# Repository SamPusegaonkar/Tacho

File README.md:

# TachoMeter

**The above code is written in Arduino C Language.**

**Description**: A tachometer is a device used to measure the rpm of a motor or any other rotating machine. The lack of a tachometer on my bike was the inspiration for this project.   <br/>

  **Apparatus**:     
  
    1. A microcontroller
    2. Multi-colored RGB LED
    3. IR sensor
    4. Some white tape
    5. Cardboard
                     
  **Instructions**: 
  
    1. Cut a circle on a piece of cardboard and attach some white tape from the radius of the circle to its end.
    2. Attach this circle on the shaft of the motor.
    3. Place in infrared sensor near the circle such that the tape passes atleast once, when the motor shaft rotates.
    4. I suck at explaning, so watch the video provided in the repo.

  **Multi-Colored RGB LED as output**:
  
    * if 0-10   rpm: then white 
    * if 10-20  rpm: then pink 
    * if 20-30  rpm: then red
    * if 30-40  rpm: then orange
    * if 40-50  rpm: then yellow
    * if 50-60  rpm: then blue
    * if 60-70  rpm: then indigo 
    * if 70-80  rpm: then green
    * if 80-90  rpm: then brown
    * if 90-100 rpm: then light blue
   
tweet @sampusegaonkar

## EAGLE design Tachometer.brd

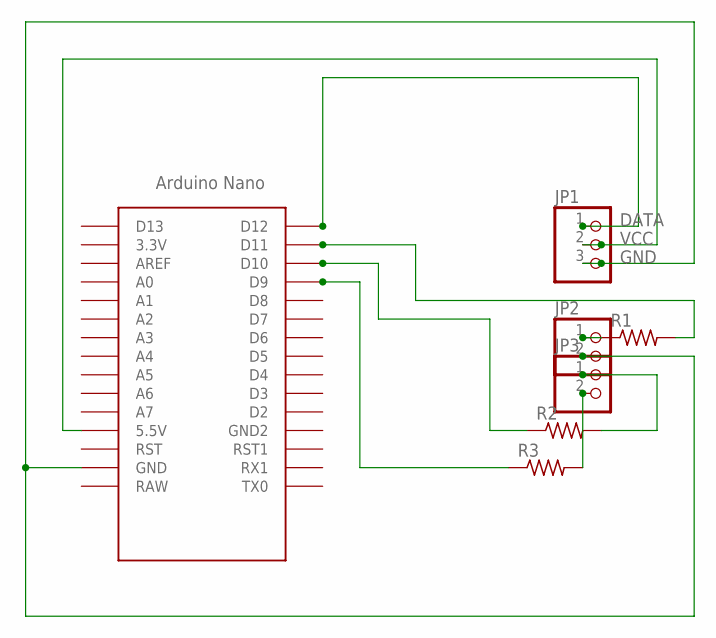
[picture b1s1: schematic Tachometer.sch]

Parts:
JP1: PINHD-1X3; 1X03
JP2, JP3: PINHD-1X2; 1X02
R1, R2, R3: R-US_0207/12; 0207/12
U$1: NANO

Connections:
DATA: JP1.1, U$1.D12
GND: JP1.3, JP2.2, U$1.GND
unnamed: JP2.1, R1.1
unnamed: JP3.2, R3.2
unnamed: JP3.1, R2.2
unnamed: R1.2, U$1.D11
unnamed: R2.1, U$1.D10
unnamed: R3.1, U$1.D9
VCC: JP1.2, U$1.5V (5.5V)

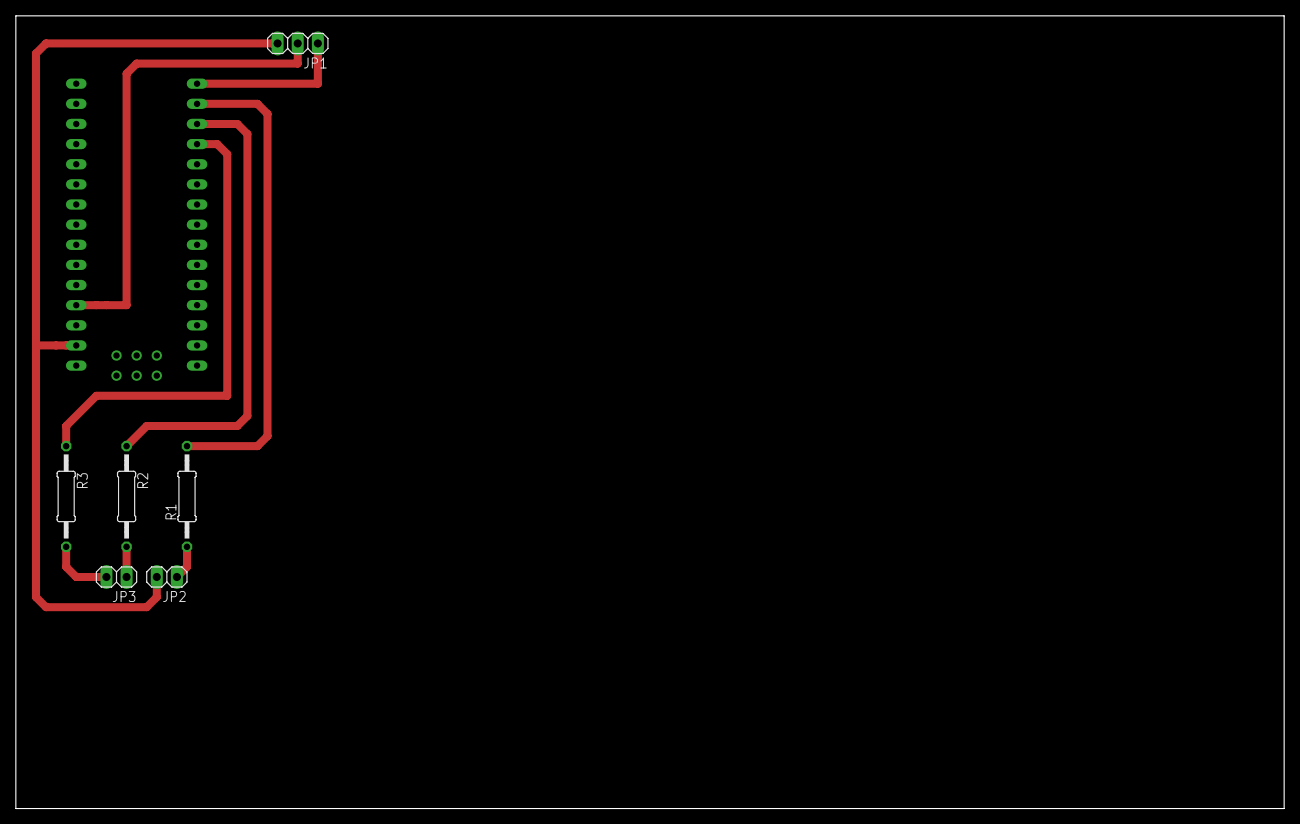
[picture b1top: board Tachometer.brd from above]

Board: 2 copper layers, 160.0 x 100.0 mm, 7 parts (0 on the bottom side), 9 nets.

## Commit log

2018-06-25 Circuit Schematic and Board View
2018-06-25 Testing the code.
    Apologies for the vertical video.
2018-06-25 Main code
2021-12-13 Set theme jekyll-theme-minimal
